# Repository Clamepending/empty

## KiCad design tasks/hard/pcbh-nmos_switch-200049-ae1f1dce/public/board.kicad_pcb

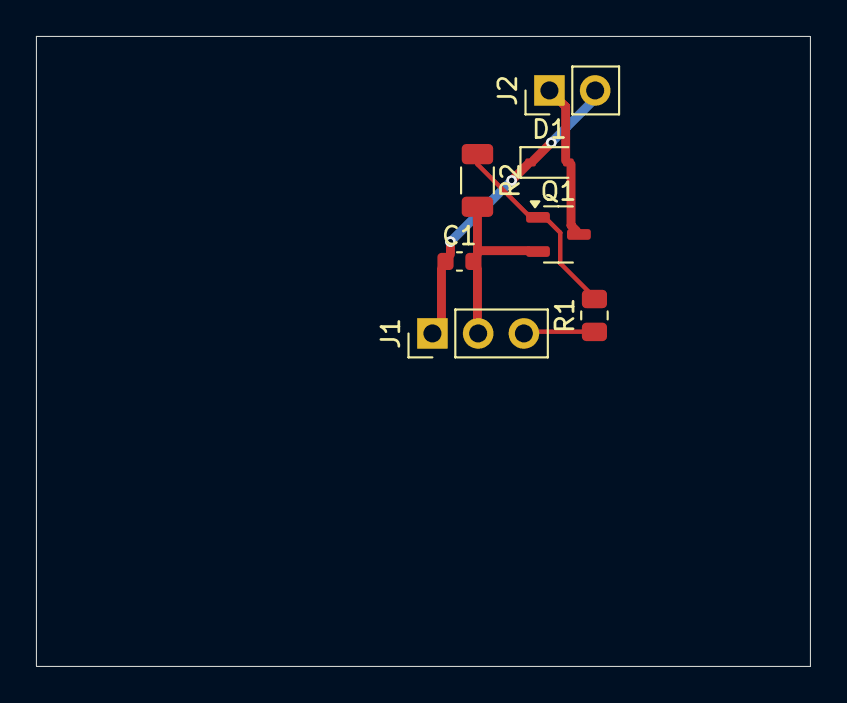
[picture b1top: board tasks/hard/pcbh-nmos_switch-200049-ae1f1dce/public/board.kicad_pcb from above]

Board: 2 copper layers, 43.0 x 35.0 mm, 7 parts (0 on the bottom side), 5 nets.

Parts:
C1: 3.3u; C_0603_1608Metric
D1: D_SOD-323
J1: PinHeader_1x03_P2.54mm_Vertical
J2: PinHeader_1x02_P2.54mm_Vertical
Q1: SOT-23-3
R1: 22; R_0805_2012Metric
R2: 330k; R_1206_3216Metric

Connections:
+24V: C1.1, D1.1, J1.1, J2.2
CTRL: J1.3, R1.1
GATE: Q1.1, R1.2, R2.1
GND: C1.2, J1.2, Q1.2, R2.2
SW: D1.2, J2.1, Q1.3

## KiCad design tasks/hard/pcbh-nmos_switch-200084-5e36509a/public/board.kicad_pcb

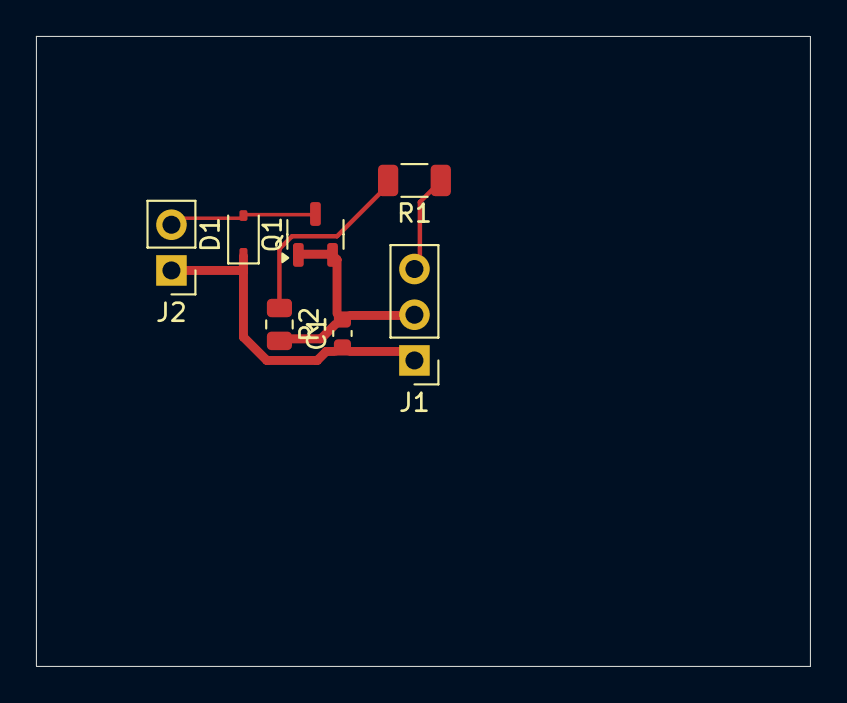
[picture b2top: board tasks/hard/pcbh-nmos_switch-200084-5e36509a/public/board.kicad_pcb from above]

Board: 2 copper layers, 43.0 x 35.0 mm, 7 parts (0 on the bottom side), 5 nets.

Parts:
C1: 2.2u; C_0603_1608Metric
D1: D_SOD-323
J1: PinHeader_1x03_P2.54mm_Vertical
J2: PinHeader_1x02_P2.54mm_Vertical
Q1: SOT-23-3
R1: 12; R_1206_3216Metric
R2: 20k; R_0805_2012Metric

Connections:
+9V: C1.1, D1.1, J1.1, J2.1
CTRL: J1.3, R1.1
GATE: R1.2, R2.1
GND: C1.2, J1.2, Q1.1, Q1.2, R2.2
SW: D1.2, J2.2, Q1.3
